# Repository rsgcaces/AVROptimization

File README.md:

# AVR Optimization

Support for RSGC ACES III (ICS4U)

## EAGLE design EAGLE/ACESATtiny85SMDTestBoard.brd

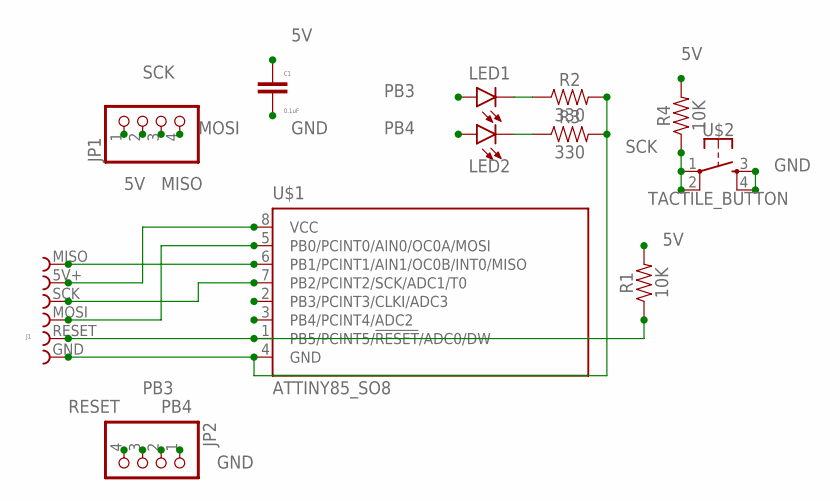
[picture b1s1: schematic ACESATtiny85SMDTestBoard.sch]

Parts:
C1: 0.1uF; C1206
J1: CONN_FPC_ISPCONNECTOR_PADS; 68610614122
JP1, JP2: PINHD-1X4; 1X04
LED1, LED2: LED_1206
R1, R4: 10K; R1206
R2, R3: 330; R1206
U$1: ATTINY85_SO8; SOIC127P798X216-8
U$2: TACTILE_BUTTON; TACTILE_BUTTON_SMD_5.2MM

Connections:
5V: C1.1, J1.5V+, JP1.1, R1.2, R4.2, U$1.8 (VCC)
GND: C1.2, J1.GND, JP2.1, R2.2, R3.2, U$1.4 (GND), U$2.3, U$2.4
MISO: J1.MISO, JP1.3, U$1.6 (PB1/PCINT1/AIN1/OC0B/INT0/MISO)
MOSI: J1.MOSI, JP1.4, U$1.5 (PB0/PCINT0/AIN0/OC0A/MOSI)
unnamed: LED1.- (C), R2.1
unnamed: LED2.- (C), R3.1
PB3: JP2.3, LED1.+ (A), U$1.2 (PB3/PCINT3/CLKI/ADC3)
PB4: JP2.2, LED2.+ (A), U$1.3 (PB4/PCINT4/ADC2)
RESET: J1.RESET, JP2.4, R1.1, U$1.1 (PB5/PCINT5/!RESET!/ADC0/DW)
SCK: J1.SCK, JP1.2, R4.1, U$1.7 (PB2/PCINT2/SCK/ADC1/T0), U$2.1, U$2.2

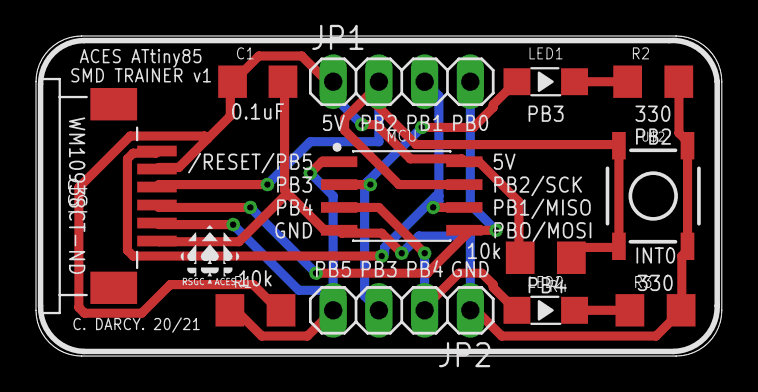
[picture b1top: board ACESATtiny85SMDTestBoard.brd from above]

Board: 2 copper layers, 38.1 x 17.8 mm, 14 parts (0 on the bottom side), 10 nets.

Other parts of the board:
U$3: MEDIUM_BSILK
U$5: SMALL_TSILK_TEXT

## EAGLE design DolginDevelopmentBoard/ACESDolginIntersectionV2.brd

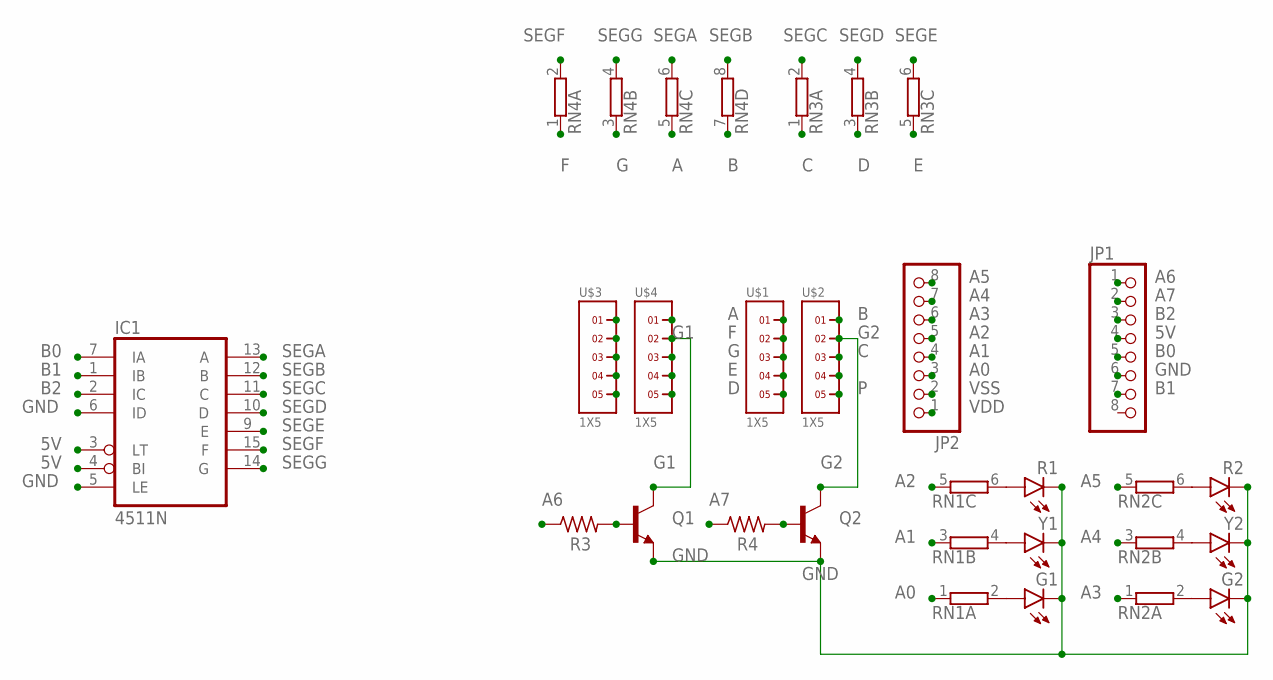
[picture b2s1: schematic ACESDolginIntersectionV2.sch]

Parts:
G1, G2: LED3MM
IC1: 4511N; DIL16
JP1, JP2: PINHD-1X8; 1X08
Q1, Q2: NPN2N3904; 2N3904
R1, R2: LED3MM
R3, R4: R-US_0207/10; 0207/10
RN1, RN2, RN3: E3R; SIL6
RN4: E4R; SIL8
U$1, U$2, U$3, U$4: 1X5
Y1, Y2: LED3MM

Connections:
5V: IC1.3 (LT), IC1.4 (BI), JP1.4
A: RN4.5 (1), U$1.1, U$3.1
A0: JP2.3, RN1.1
A1: JP2.4, RN1.3 (1)
A2: JP2.5, RN1.5 (1)
A3: JP2.6, RN2.1
A4: JP2.7, RN2.3 (1)
A5: JP2.8, RN2.5 (1)
A6: JP1.1, R3.1
A7: JP1.2, R4.1
B: RN4.7 (1), U$2.1, U$4.1
B0: IC1.7 (IA), JP1.5
B1: IC1.1 (IB), JP1.7
B2: IC1.2 (IC), JP1.3
C: RN3.1, U$2.3, U$4.3
D: RN3.3 (1), U$1.5, U$3.5
E: RN3.5 (1), U$1.4, U$3.4
F: RN4.1, U$1.2, U$3.2
G: RN4.3 (1), U$1.3, U$3.3
G1: Q1.C, U$4.2
G2: Q2.C, U$2.2
GND: G1.K (C), G2.K (C), IC1.5 (LE), IC1.6 (ID), JP1.6, Q1.E, Q2.E, R1.K (C), R2.K (C), U$2.4, U$4.4, Y1.K (C), Y2.K (C)
unnamed: G1.A, RN1.2
unnamed: RN1.4 (2), Y1.A
unnamed: R1.A, RN1.6 (2)
unnamed: G2.A, RN2.2
unnamed: RN2.4 (2), Y2.A
unnamed: R2.A, RN2.6 (2)
P: U$2.5, U$4.5
Q1BASE: Q1.B, R3.2
Q2BASE: Q2.B, R4.2
SEGA: IC1.13 (A), RN4.6 (2)
SEGB: IC1.12 (B), RN4.8 (2)
SEGC: IC1.11 (C), RN3.2
SEGD: IC1.10 (D), RN3.4 (2)
SEGE: IC1.9 (E), RN3.6 (2)
SEGF: IC1.15 (F), RN4.2
SEGG: IC1.14 (G), RN4.4 (2)
VDD: IC1.16 (VDD), JP2.1
VSS: IC1.8 (VSS), JP2.2

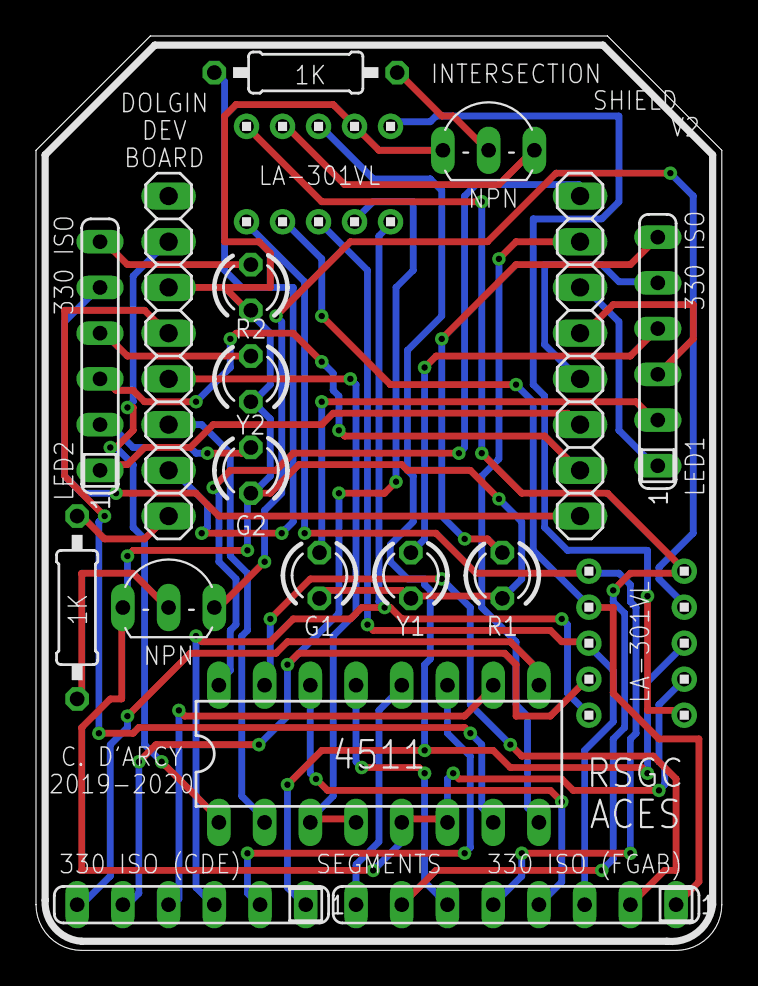
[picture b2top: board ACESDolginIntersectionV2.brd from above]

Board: 2 copper layers, 38.1 x 50.8 mm, 22 parts (0 on the bottom side), 40 nets.

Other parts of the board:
U$5: ACES_LOGO_MEDIUM

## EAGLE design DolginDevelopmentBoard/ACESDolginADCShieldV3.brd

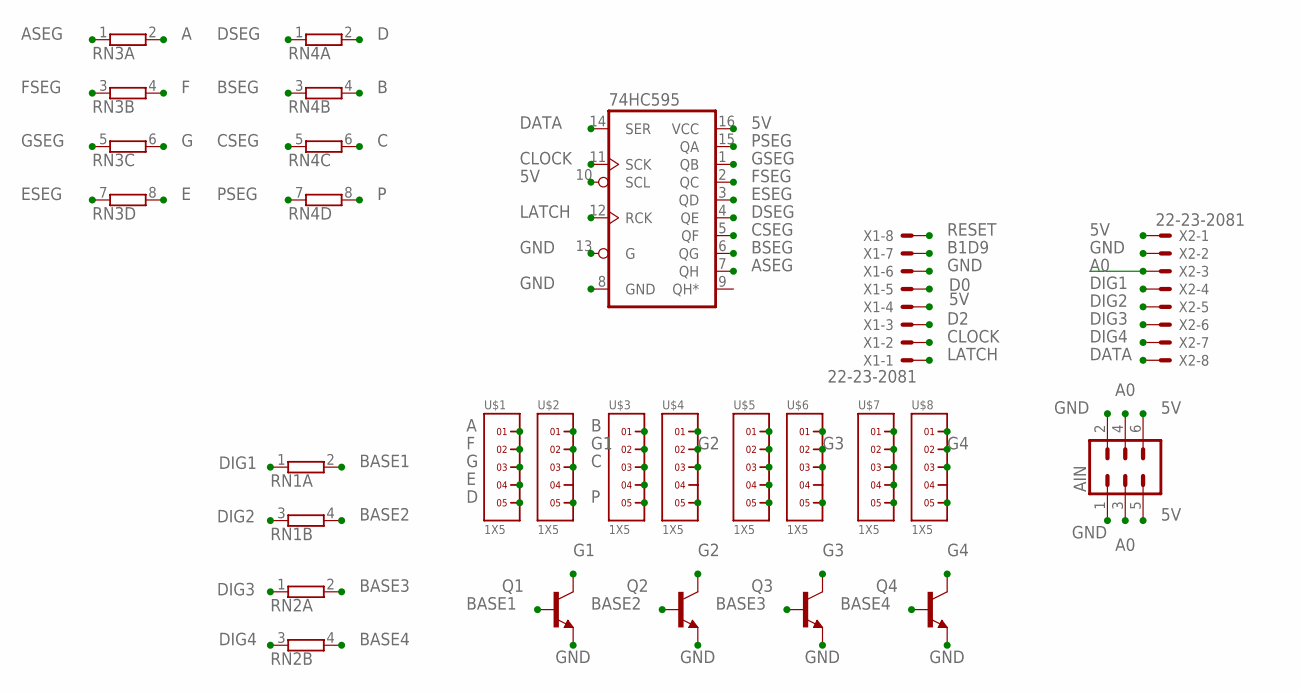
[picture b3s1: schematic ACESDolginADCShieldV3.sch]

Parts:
74HC595: 595; DIL16
AIN: CONN_03X2FEMALE; 2X3
Q1, Q2, Q3, Q4: NPN2N3904; 2N3904
RN1, RN2: E2R; SIL4
RN3, RN4: E4R; SIL8
U$1, U$2, U$3, U$4, U$5, U$6, U$7, U$8: 1X5
X1, X2: 22-23-2081

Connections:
5V: 74HC595.10 (SCL), 74HC595.16 (VCC), AIN.5, AIN.6, X1.4, X2.1
A: RN3.2, U$1.1, U$3.1, U$5.1, U$7.1
A0: AIN.3, AIN.4, X2.3
ASEG: 74HC595.7 (QH), RN3.1
B: RN4.4 (2), U$2.1, U$4.1, U$6.1, U$8.1
B1D9: X1.7
BASE1: Q1.B, RN1.2
BASE2: Q2.B, RN1.4 (2)
BASE3: Q3.B, RN2.2
BASE4: Q4.B, RN2.4 (2)
BSEG: 74HC595.6 (QG), RN4.3 (1)
C: RN4.6 (2), U$2.3, U$4.3, U$6.3, U$8.3
CLOCK: 74HC595.11 (SCK), X1.2
CSEG: 74HC595.5 (QF), RN4.5 (1)
D: RN4.2, U$1.5, U$3.5, U$5.5, U$7.5
D0: X1.5
D2: X1.3
DATA: 74HC595.14 (SER), X2.8
DIG1: RN1.1, X2.4
DIG2: RN1.3 (1), X2.5
DIG3: RN2.1, X2.6
DIG4: RN2.3 (1), X2.7
DSEG: 74HC595.4 (QE), RN4.1
E: RN3.8 (2), U$1.4, U$3.4, U$5.4, U$7.4
ESEG: 74HC595.3 (QD), RN3.7 (1)
F: RN3.4 (2), U$1.2, U$3.2, U$5.2, U$7.2
FSEG: 74HC595.2 (QC), RN3.3 (1)
G: RN3.6 (2), U$1.3, U$3.3, U$5.3, U$7.3
G1: Q1.C, U$2.2
G2: Q2.C, U$4.2
G3: Q3.C, U$6.2
G4: Q4.C, U$8.2
GND: 74HC595.8 (GND), 74HC595.13 (G), AIN.1, AIN.2, Q1.E, Q2.E, Q3.E, Q4.E, X1.6, X2.2
GSEG: 74HC595.1 (QB), RN3.5 (1)
LATCH: 74HC595.12 (RCK), X1.1
P: RN4.8 (2), U$2.5, U$4.5, U$6.5, U$8.5
PSEG: 74HC595.15 (QA), RN4.7 (1)
RESET: X1.8

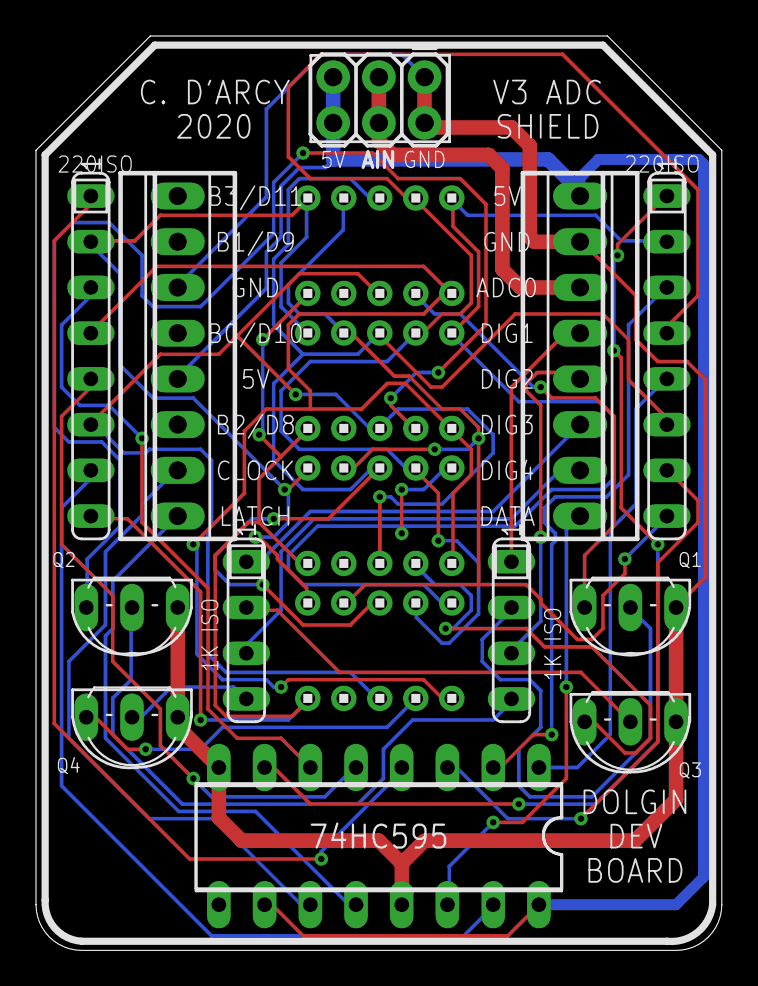
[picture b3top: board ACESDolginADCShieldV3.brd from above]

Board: 2 copper layers, 38.1 x 50.8 mm, 21 parts (0 on the bottom side), 34 nets.

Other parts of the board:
U$9: ACES_LOGO_MEDIUM

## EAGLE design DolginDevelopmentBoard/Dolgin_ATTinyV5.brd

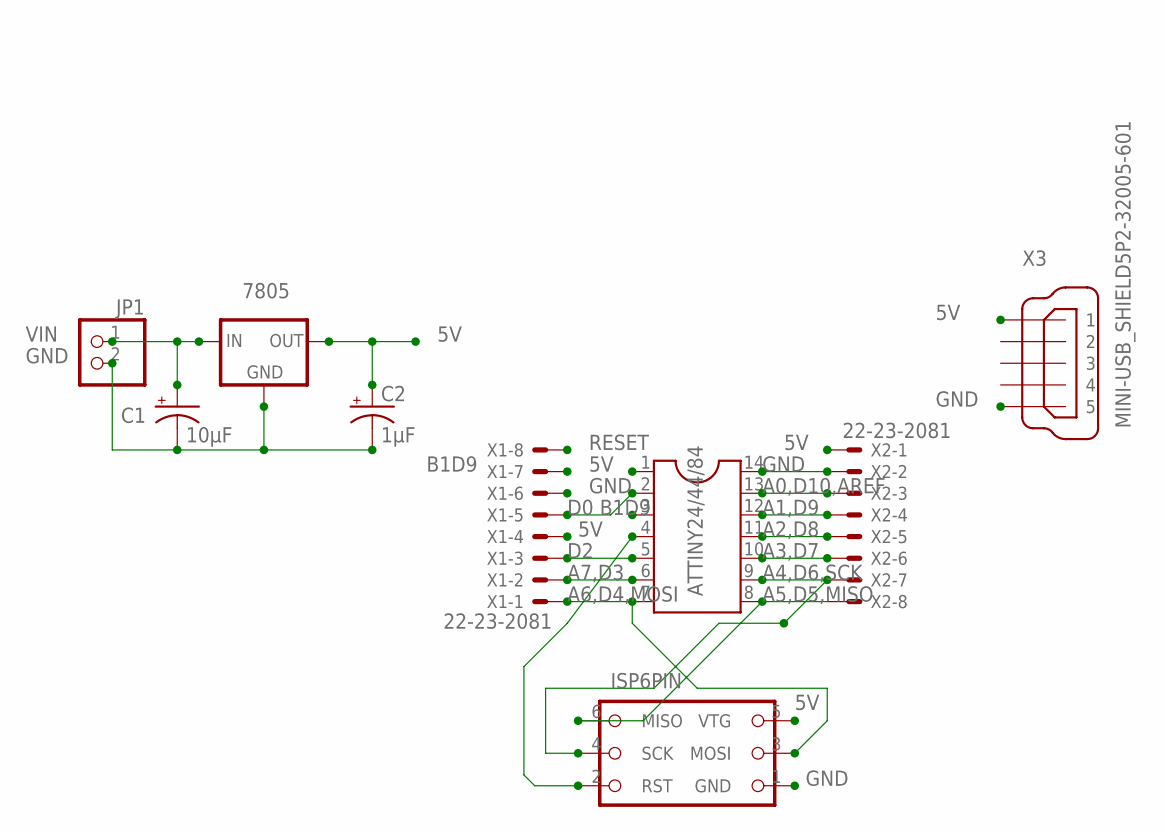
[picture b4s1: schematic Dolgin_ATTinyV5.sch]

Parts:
7805: LM78XX; 78XXL
ATTINY24/44/84: DIL14
C1: 10µF; CPOL-RADIAL-2.5MM-5MM
C2: 1µF; CPOL-RADIAL-2.5MM-5MM
H1: ISP_HEADER; ICSP
JP1: PINHD-1X2; 1X02
X1, X2: 22-23-2081
X3: MINI-USB_SHIELD5P2-32005-601; 32005-601

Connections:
5V: 7805.OUT, ATTINY24/44/84.1, C2.1 (+), H1.5 (VTG), X1.4, X2.1, X3.1
A0,D10,AREF: ATTINY24/44/84.13, X2.3
A1,D9: ATTINY24/44/84.12, X2.4
A2,D8: ATTINY24/44/84.11, X2.5
A3,D7: ATTINY24/44/84.10, X2.6
A4,D6,SCK: ATTINY24/44/84.9, H1.4 (SCK), X2.7
A5,D5,MISO: ATTINY24/44/84.8, H1.6 (MISO), X2.8
A6,D4,MOSI: ATTINY24/44/84.7, H1.3 (MOSI), X1.1
A7,D3: ATTINY24/44/84.6, X1.2
B1D9: ATTINY24/44/84.3, X1.7
D0: ATTINY24/44/84.2, X1.5
D2: ATTINY24/44/84.5, X1.3
GND: 7805.GND, ATTINY24/44/84.14, C1.2 (-), C2.2 (-), H1.1 (GND), JP1.2, X1.6, X2.2, X3.5
RESET: ATTINY24/44/84.4, H1.2 (RST), X1.8
VIN: 7805.IN, C1.1 (+), JP1.1

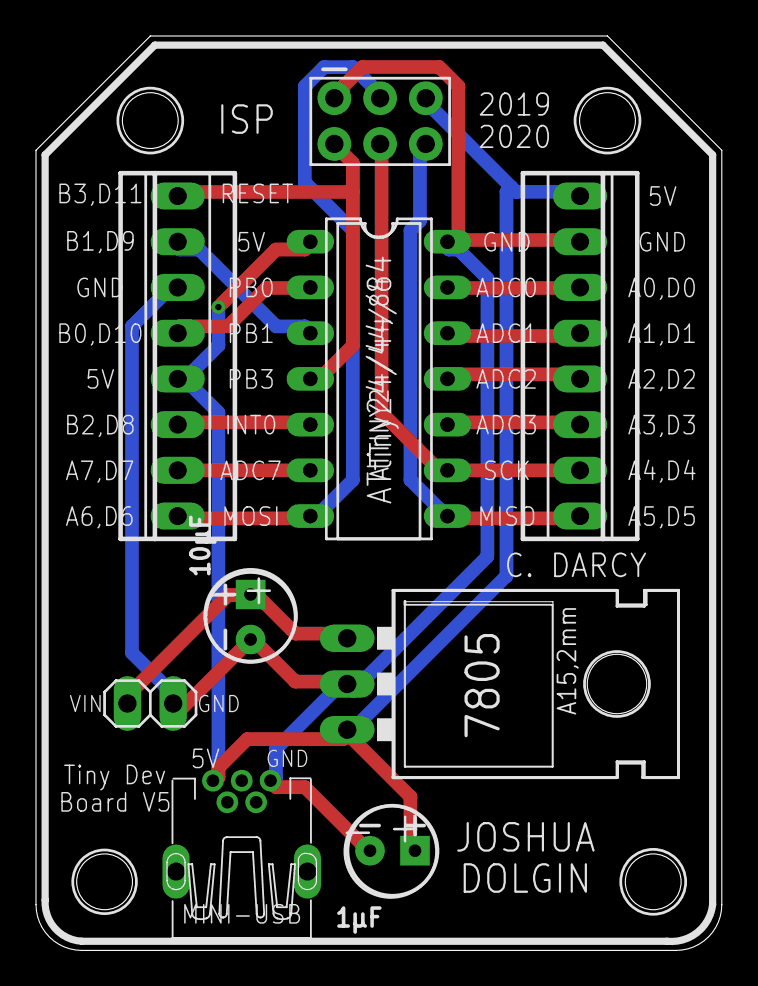
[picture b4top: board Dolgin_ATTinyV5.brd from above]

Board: 2 copper layers, 38.1 x 50.8 mm, 10 parts (1 on the bottom side), 15 nets.

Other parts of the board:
U$1: ACES_LOGO_SMALL

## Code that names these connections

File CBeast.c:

/*
 * CBeast.c
 * Example of AVR-gcc C Code to present the value of pi on 'The Beast'.
 *'The Beast' is a PCB designed to present a 12-digit PoV display using 
 * a normal 595 shift registers for the segment and TPIC6C595 Power logic current sink 
 * Created: 8/10/2018 1:10:28 PM
 * Author: Chris Darcy
 */ 

#include <avr/io.h>
#define F_CPU 16000000UL  // 16 MHz
#include <util/delay.h>

uint8_t latch = 1<<PB2;			//digital pin 10
uint8_t clock = 1<<PB3;			//digital pin 11
uint8_t data = 1<<PB4;			//digital pin 12

// Seven Segment Order:dGFEDCBA
uint8_t dp = 1<<7;
//Assemble the hexadecimal segment maps into single array...
uint8_t  segMaps[] = {0b00111111,0b00000110, 0b01011011, 0b01001111,0b01100110,0b01101101,0b01111100,0b00000111,0b01111111,0b01100111,
	                  0b01110111,0b01111100,0b00111001,0b01011110,0b01111001,0b01110001};

char display[] = "314159265539";  //Sample...

//my 'super' shiftout (23 bits are shifted in one go)
void shiftOut(uint8_t d, uint8_t c, uint8_t l, uint32_t segMap, uint32_t digit ){
	uint32_t bits = (segMap<<16) | digit;
	// assemble the 23-bit shift out value from the segMap and the respective digit
	//pull latch low...
	PORTB &= ~latch;
	//synchronously clock in the data bits 
	for (uint32_t mask=1L<<23; mask>0; mask>>=1)	{
		PORTB &= ~clock;
		// should the data bit be set or clear?
		if (bits & mask)
			PORTB |= data;
		else 
			PORTB &= ~data;
		PORTB |= clock;
	}	
	//pull latch high to present present flipflops on the output pins...
	PORTB |= latch;
}

int main(void)
{
  // Let's use three pins of portB for the shifting...
  DDRB = 0xFF;
  uint8_t i = 0;
  uint32_t segments; 
  while(1) {
	segments = segMaps[display[i]-48];
	if (!i) segments |= dp;  //add decimal point on the 3 for pi 
	shiftOut(data,clock,latch,segments,1L<<(11-i));
	i = (i+1) % 12;
  }
}

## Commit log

2018-08-04 Created: 2018 08 04
2018-08-04 Created: 2018 08 01
2018-08-08 2018 08 08
2018-08-10 Just before we begin: C
2018-08-11 Created: 2018 08 11
2018-08-13 Created: 2018 08 13
2018-08-16 Created: 2018 08 16
2018-08-17 Created: 2018 08 17
2018-08-21 Created: 2018 08 21
2019-01-25 Support for External Interrupts
2019-01-25 Sets the current time and date for the DS1307 RTC
2019-02-02 Compares Hardware and Software shiftout strategies
2019-02-02 Pits (software) shiftOut against (hardware) SPI
2019-02-02 Interrupt-driven coding of SPI transmission to a shift register
2019-02-14 Test Code for MorlandBargraphSMTV1
2019-04-02 Update: 2019 04 02
2019-04-08 Added: 2019 04 08
2019-04-25 Include file developed from Weinman's (Alfred State) blog code
    Developed for use for the first time in conjunction with the 2018/19 ICS4U DC Fan Project to display ADC and PWN data.
2019-04-29 Updated: 2019 04 29
2019-05-31 DDB Design Files
2019-10-01 DDB Version 5 EAGLE files
2019-10-02 Latest versions
2019-10-02 Fusion 360 V4 Case file
2020-01-13 Added: 2020 01 13
2020-03-12 Added: 2020 03 12
    EAGLE Files for the ATtiny85 SMD Test Board PCB/Project developed and first adminstered to the 2019/2020 ICS4U ACES.
2020-10-04 Updated: 2020 10 04
    Support forthose students wishing to wire their own EEPROM prototype.
2020-10-06 Updated: 2020 10 06
    AT28C16 EEPROM code compatible with RSGC ACES EEPROM Burner Shield v1 (January 2020)
2020-10-08 2020 10 08
    Added support for flashing 7-segment maps for hex digits to AT28C16A EEPROMs.
2020-10-08 2020 10 08
2020-10-09 2020 10 09
    Tested successfully on RSGC ACES UNO Burner Shield.
2020-10-10 2020 10 10
    Tidied up comments.
2020-10-31 Updated: 2020 10 31
    CAT28C16 EEPROM Shield Code Updated
2020-11-03 Update AT28C16EEPROMShieldVersion.ino
    Added USER function SHL which shifts A left one on the strength of the ALU's A PLUS A function

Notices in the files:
parts and their libraries:
SparkFun-Connectors: Licensing: Creative Commons ShareAlike 4.0 International - https://creativecommons.org/licenses/by-sa/4.0
